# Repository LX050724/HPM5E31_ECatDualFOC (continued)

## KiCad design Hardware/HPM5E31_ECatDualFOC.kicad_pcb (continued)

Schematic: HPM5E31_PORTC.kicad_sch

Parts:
U3: HPM5E31IGN1; BGA-196_14x14_12.0x12.0mm_P0.8mm

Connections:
/ENCODER_CONN_A/ENC.CLK: U3.B7 (PC04/UART1.CTS/SPI0.SCLK/MCAN1.RXD/ESC0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); also elsewhere on the board
/ENCODER_CONN_A/ENC.CS: U3.A8 (PC05/GPTMR1.COMP2/UART1.DE/UART1.RTS/SP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); also elsewhere on the board
/ENCODER_CONN_A/ENC.MISO: U3.B8 (PC06/GPTMR0.CAPT0/UART1.RXD/I2C3.SDA/SP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); also elsewhere on the board
/ENCODER_CONN_A/ENC.MOSI: U3.A9 (PC07/GPTMR0.COMP0/UART1.TXD/I2C3.SCL/SP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); also elsewhere on the board
/ENCODER_CONN_B/ENC.CLK: U3.A11 (PC20/UART5.CTS/SPI3.SCLK/ESC0.GPI43/ESC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); also elsewhere on the board
/ENCODER_CONN_B/ENC.CS: U3.B11 (PC21/GPTMR3.COMP2/UART5.DE/UART5.RTS/SP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); also elsewhere on the board
/ENCODER_CONN_B/ENC.MISO: U3.A12 (PC22/GPTMR2.CAPT0/UART5.RXD/SPI3.MISO/E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); also elsewhere on the board
/ENCODER_CONN_B/ENC.MOSI: U3.A13 (PC23/GPTMR2.COMP0/UART5.TXD/SPI3.MOSI/E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); also elsewhere on the board
/HPM5E31_TOP/CAN0.RXD: U3.A6 (PC01/GPTMR1.CAPT0/UART0.RXD/MCAN0.RXD/E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); also elsewhere on the board
/HPM5E31_TOP/CAN0.TXD: U3.B5 (PC00/GPTMR1.COMP0/UART0.TXD/MCAN0.TXD/E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); also elsewhere on the board
/HPM5E31_TOP/FLASH.CS0: U3.D13 (PC27/UART6.CTS/SPI2.CS0/ESC0.GPI36/ESC0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); also elsewhere on the board
/HPM5E31_TOP/FLASH.D0: U3.E13 (PC29/GPTMR3.COMP3/UART7.DE/UART7.RTS/SP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); also elsewhere on the board
/HPM5E31_TOP/FLASH.D1: U3.E14 (PC28/UART7.CTS/SPI2.MISO/ESC0.GPI35/ESC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); also elsewhere on the board
/HPM5E31_TOP/FLASH.D2: U3.F14 (PC30/UART7.RXD/SPI2.DAT2/ESC0.GPI33/ESC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); also elsewhere on the board
/HPM5E31_TOP/FLASH.D3: U3.F13 (PC31/GPTMR2.COMP3/UART7.TXD/SPI2.DAT3/E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); also elsewhere on the board
/HPM5E31_TOP/FLASH.SCLK: U3.D14 (PC26/GPTMR2.COMP2/UART6.DE/UART6.RTS/SP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); also elsewhere on the board
/HPM5E31_TOP/RS485_3.DE: U3.C7 (PC13/GPTMR1.COMP3/UART3.DE/UART3.RTS/I2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); also elsewhere on the board
/HPM5E31_TOP/RS485_3.DI: U3.C8 (PC15/GPTMR0.COMP3/UART3.TXD/SPI1.DAT3/M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); also elsewhere on the board
/HPM5E31_TOP/RS485_3.RO: U3.D7 (PC14/UART3.RXD/SPI1.DAT2/MCAN3.RXD/ESC0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); also elsewhere on the board
PC2: U3.B6 (PC02/GPTMR1.COMP1/UART0.DE/UART0.RTS/I2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); also elsewhere on the board
PC3: U3.A7 (PC03/GPTMR1.CAPT1/UART0.CTS/I2C2.SDA/SP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); also elsewhere on the board
PC8: U3.B9 (PC08/GPTMR0.COMP1/UART2.TXD/I2C0.SCL/SP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); also elsewhere on the board
PC9: U3.C5 (PC09/GPTMR0.CAPT1/UART2.RXD/I2C0.SDA/SP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); also elsewhere on the board
PC10: U3.D5 (PC10/GPTMR0.COMP2/UART2.DE/UART2.RTS/SP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); also elsewhere on the board
PC11: U3.C6 (PC11/UART2.CTS/SPI1.CS0/ESC0.GPI52/ESC0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); also elsewhere on the board
PC12: U3.D6 (PC12/UART3.CTS/I2C1.SDA/SPI1.MISO/ESC0.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); also elsewhere on the board
PC16: U3.D8 (PC16/GPTMR3.COMP0/UART4.TXD/ESC0.GPI47/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)
PC17: U3.C9 (PC17/GPTMR3.CAPT0/UART4.RXD/ESC0.GPI46/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); also elsewhere on the board
PC18: U3.A10 (PC18/GPTMR3.COMP1/UART4.DE/UART4.RTS/ES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); also elsewhere on the board
PC19: U3.B10 (PC19/GPTMR3.CAPT1/UART4.CTS/SPI2.CS3/ES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)
PC24: U3.B14 (PC24/GPTMR2.COMP1/UART6.TXD/SPI2.CS2/ES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)
PC25: U3.C14 (PC25/GPTMR2.CAPT1/UART6.RXD/SPI2.CS1/ES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)

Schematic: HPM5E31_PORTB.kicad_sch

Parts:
U3: HPM5E31IGN1; BGA-196_14x14_12.0x12.0mm_P0.8mm

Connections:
/ETHERNET_PHY_P0/MII.LINK: U3.B1 (PB25/ESC0.CTR5/XPI0.CA_DQS/SDM0.DAT3/ET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); also elsewhere on the board
/ETHERNET_PHY_P0/MII.RXC: U3.C2 (PB05/MCAN1.TXD/ESC0.P0_RXCK/PWM0.P5/TRG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); also elsewhere on the board
/ETHERNET_PHY_P0/MII.RXD0: U3.E2 (PB01/MCAN0.RXD/ESC0.P0_RXD0/PWM0.P1/TRG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); also elsewhere on the board
/ETHERNET_PHY_P0/MII.RXD1: U3.D1 (PB02/I2C2.SCL/MCAN0.STBY/ESC0.P0_RXD1/P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); also elsewhere on the board
/ETHERNET_PHY_P0/MII.RXD2: U3.D2 (PB03/I2C2.SDA/MCAN1.STBY/ESC0.P0_RXD2/P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); also elsewhere on the board
/ETHERNET_PHY_P0/MII.RXD3: U3.C1 (PB04/MCAN1.RXD/ESC0.P0_RXD3/PWM0.P4/TRG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); also elsewhere on the board
/ETHERNET_PHY_P0/MII.RX_DV: U3.E1 (PB00/MCAN0.TXD/ESC0.P0_RXDV/PWM0.P0/TRG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); also elsewhere on the board
/ETHERNET_PHY_P0/MII.TXC: U3.E3 (PB06/I2C3.SDA/ESC0.P0_TXCK/PWM0.P6/TRGM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); also elsewhere on the board
/ETHERNET_PHY_P0/MII.TXD0: U3.E4 (PB07/I2C3.SCL/ESC0.P0_TXD0/PWM0.P7/TRGM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); also elsewhere on the board
/ETHERNET_PHY_P0/MII.TXD1: U3.D3 (PB08/I2C0.SCL/MCAN2.TXD/ESC0.P0_TXD1/PW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); also elsewhere on the board
/ETHERNET_PHY_P0/MII.TXD2: U3.D4 (PB09/I2C0.SDA/MCAN2.RXD/ESC0.P0_TXD2/PW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); also elsewhere on the board
/ETHERNET_PHY_P0/MII.TXD3: U3.C3 (PB10/MCAN2.STBY/ESC0.P0_TXD3/PWM1.P2/TR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); also elsewhere on the board
/ETHERNET_PHY_P0/MII.TXEN: U3.C4 (PB11/ESC0.P0_TXEN/PWM1.P3/TRGM.P11/ETH0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); also elsewhere on the board
/ETHERNET_PHY_P2/MII.RST: U3.A2 (PB24/ESC0.CTR4/XPI0.CA_CS1/SDM0.CLK3/ET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); also elsewhere on the board
PB26: U3.A3 (PB26/ESC0.CTR6/XPI0.CA_D2/QEI1.H1/SDM0.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); also elsewhere on the board
PB27: U3.B2 (PB27/ESC0.CTR7/XPI0.CA_D0/QEI1.F/SDM0.D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); also elsewhere on the board
PB28: U3.A4 (PB28/ESC0.CTR8/XPI0.CA_D1/QEI1.H0/SDM0.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); also elsewhere on the board
PB29: U3.B3 (PB29/XPI0.CA_SCLK/QEI1.Z/SDM0.DAT1/ETH0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); also elsewhere on the board
PB30: U3.A5 (PB30/ESC0.CTR7/XPI0.CA_CS0/QEI1.A/SDM0.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); also elsewhere on the board
PB31: U3.B4 (PB31/ESC0.CTR8/XPI0.CA_D3/QEI1.B/SDM0.D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); also elsewhere on the board

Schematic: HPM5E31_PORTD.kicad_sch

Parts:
U3: HPM5E31IGN1; BGA-196_14x14_12.0x12.0mm_P0.8mm

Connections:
/ENCODER_CONN_A/ENC.A: U3.B13 (PD07/I2C3.SCL/ESC0.GPI24/ESC0.GPO39/PPI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); also elsewhere on the board
/ENCODER_CONN_A/ENC.B: U3.C12 (PD06/I2C3.SDA/ESC0.GPI25/ESC0.GPO38/PPI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); also elsewhere on the board
/ENCODER_CONN_A/ENC.Z: U3.B12 (PD05/MCAN1.TXD/ESC0.GPI26/ESC0.GPO37/PP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); also elsewhere on the board
/ENCODER_CONN_B/ENC.A: U3.K12 (PD30/ESC0.GPI01/ESC0.GPO62/PPI0.DQ01/ES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); also elsewhere on the board
/ENCODER_CONN_B/ENC.B: U3.K11 (PD31/ESC0.GPI00/ESC0.GPO63/PPI0.DQ00/ES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); also elsewhere on the board
/ENCODER_CONN_B/ENC.PWR: U3.F11 (PD13/I2C1.SCL/MCAN3.STBY/ESC0.GPI18/ESC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); also elsewhere on the board
/ENCODER_CONN_B/ENC.U: U3.F12 (PD12/I2C1.SDA/ESC0.GPI19/ESC0.GPO44/PPI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); also elsewhere on the board
/ENCODER_CONN_B/ENC.V: U3.E12 (PD10/MCAN2.STBY/ESC0.GPI21/ESC0.GPO42/P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); also elsewhere on the board
/ENCODER_CONN_B/ENC.W: U3.E11 (PD11/ESC0.GPI20/ESC0.GPO43/PPI0.CS2/PWM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); also elsewhere on the board
/ENCODER_CONN_B/ENC.Z: U3.J10 (PD29/ESC0.GPI02/ESC0.GPO61/PPI0.DQ02/ES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); also elsewhere on the board
/ETHERNET_PHY_P2/MII.RXC: U3.J13 (PD21/ESC0.GPI10/ESC0.GPO53/PPI0.DQ13/ES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); also elsewhere on the board
/ETHERNET_PHY_P2/MII.RXD0: U3.H14 (PD17/ESC0.GPI14/ESC0.GPO49/PPI0.DQ09/ES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); also elsewhere on the board
/ETHERNET_PHY_P2/MII.RXD1: U3.H13 (PD18/ESC0.GPI13/ESC0.GPO50/PPI0.DQ12/ES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); also elsewhere on the board
/ETHERNET_PHY_P2/MII.RXD2: U3.H12 (PD19/ESC0.GPI12/ESC0.GPO51/PPI0.DQ11/ES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); also elsewhere on the board
/ETHERNET_PHY_P2/MII.RXD3: U3.J14 (PD20/ESC0.GPI11/ESC0.GPO52/PPI0.DQ14/ES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); also elsewhere on the board
/ETHERNET_PHY_P2/MII.RX_DV: U3.G12 (PD16/ESC0.GPI15/ESC0.GPO48/PPI0.DQ10/ES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); also elsewhere on the board
/ETHERNET_PHY_P2/MII.RX_ER: U3.J12 (PD22/ESC0.GPI09/ESC0.GPO54/PPI0.DQ15/ES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); also elsewhere on the board
/ETHERNET_PHY_P2/MII.TXC: U3.F10 (PD23/ESC0.GPI08/ESC0.GPO55/PPI0.DM0/ESC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); also elsewhere on the board
/ETHERNET_PHY_P2/MII.TXD0: U3.G11 (PD24/ESC0.GPI07/ESC0.GPO56/PPI0.DQ06/ES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); also elsewhere on the board
/ETHERNET_PHY_P2/MII.TXD1: U3.G10 (PD25/ESC0.GPI06/ESC0.GPO57/PPI0.DQ07/ES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); also elsewhere on the board
/ETHERNET_PHY_P2/MII.TXD2: U3.H11 (PD26/ESC0.GPI05/ESC0.GPO58/PPI0.DQ05/ES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); also elsewhere on the board
/ETHERNET_PHY_P2/MII.TXD3: U3.H10 (PD27/ESC0.GPI04/ESC0.GPO59/PPI0.DQ04/ES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); also elsewhere on the board
/ETHERNET_PHY_P2/MII.TXEN: U3.J11 (PD28/ESC0.GPI03/ESC0.GPO60/PPI0.DQ03/ES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); also elsewhere on the board
/HPM5E31_TOP/CAN3.RXD: U3.G14 (PD14/MCAN3.RXD/ESC0.GPI17/ESC0.GPO46/PP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); also elsewhere on the board
/HPM5E31_TOP/CAN3.TXD: U3.G13 (PD15/MCAN3.TXD/ESC0.GPI16/ESC0.GPO47/PP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); also elsewhere on the board
PD0: U3.D9 (PD00/MCAN0.TXD/ESC0.GPI31/ESC0.GPO32/PP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)
PD1: U3.C10 (PD01/MCAN0.RXD/ESC0.GPI30/ESC0.GPO33/PP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); also elsewhere on the board
PD2: U3.D10 (PD02/I2C2.SCL/MCAN0.STBY/ESC0.GPI29/ESC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); also elsewhere on the board
PD3: U3.C11 (PD03/I2C2.SDA/MCAN1.STBY/ESC0.GPI28/ESC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); also elsewhere on the board
PD4: U3.D11 (PD04/MCAN1.RXD/ESC0.GPI27/ESC0.GPO36/PP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); also elsewhere on the board
PD8: U3.C13 (PD08/I2C0.SCL/MCAN2.TXD/ESC0.GPI23/ESC0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)
PD9: U3.D12 (PD09/I2C0.SDA/MCAN2.RXD/ESC0.GPI22/ESC0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); also elsewhere on the board

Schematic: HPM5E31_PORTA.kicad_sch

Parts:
C5, C6, C7, C8: 100nF,10V; C_0201_0603Metric
U3: HPM5E31IGN1; BGA-196_14x14_12.0x12.0mm_P0.8mm

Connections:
+3.3V: C5.1, C6.1, C7.1, C8.1, U3.E6 (VIO_B01), U3.E7 (VIO_B01), U3.E8 (VIO_B01), U3.E9 (VIO_B01), U3.K6 (VIO_B01); also elsewhere on the board
/ENCODER_CONN_A/ENC.PWR: U3.K2 (PA19/GPTMR3.CAPT1/UART4.CTS/SPI3.CS3/ES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); also elsewhere on the board
/ENCODER_CONN_A/ENC.U: U3.H1 (PA22/GPTMR2.CAPT0/UART5.RXD/SPI2.MISO/E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); also elsewhere on the board
/ENCODER_CONN_A/ENC.V: U3.J2 (PA21/GPTMR3.COMP2/UART5.DE/UART5.RTS/SP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); also elsewhere on the board
/ENCODER_CONN_A/ENC.W: U3.J1 (PA20/UART5.CTS/SPI2.SCLK/ESC0.P0_RXD3/S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); also elsewhere on the board
/ETHERNET_PHY_P0/MII.RX_ER: U3.H2 (PA23/GPTMR2.COMP0/UART5.TXD/SPI2.MOSI/E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); also elsewhere on the board
/ETHERNET_PHY_P2/MII.MDC: U3.H5 (PA31/GPTMR2.COMP3/UART7.TXD/SPI3.DAT3/E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); also elsewhere on the board
/ETHERNET_PHY_P2/MII.MDIO: U3.H4 (PA30/UART7.RXD/SPI3.DAT2/ESC0.MDIO/ETH0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); also elsewhere on the board
/HPM5E31_TOP/RS485_4.DE: U3.K1 (PA18/GPTMR3.COMP1/UART4.DE/UART4.RTS/ES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); also elsewhere on the board
/HPM5E31_TOP/RS485_4.DI: U3.L1 (PA16/GPTMR3.COMP0/UART4.TXD/ESC0.P0_RXD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); also elsewhere on the board
/HPM5E31_TOP/RS485_4.RO: U3.L2 (PA17/GPTMR3.CAPT0/UART4.RXD/ESC0.P0_RXD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); also elsewhere on the board
/HPM5E31_TOP/RS485_6.DE: U3.J3 (PA26/GPTMR2.COMP2/UART6.DE/UART6.RTS/SP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); also elsewhere on the board
/HPM5E31_TOP/RS485_6.DI: U3.K3 (PA24/GPTMR2.COMP1/UART6.TXD/SPI3.CS2/ES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); also elsewhere on the board
/HPM5E31_TOP/RS485_6.RO: U3.K4 (PA25/GPTMR2.CAPT1/UART6.RXD/SPI3.CS1/ES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); also elsewhere on the board
GND: C5.2, C6.2, C7.2, C8.2; also elsewhere on the board
PA0: U3.G2 (PA00/GPTMR1.COMP0/UART0.TXD/MCAN0.TXD/P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); also elsewhere on the board
PA1: U3.G3 (PA01/GPTMR1.CAPT0/UART0.RXD/MCAN0.RXD/P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); also elsewhere on the board
PA2: U3.G4 (PA02/GPTMR1.COMP1/UART0.DE/UART0.RTS/I2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); also elsewhere on the board
PA3: U3.G5 (PA03/GPTMR1.CAPT1/UART0.CTS/I2C2.SDA/MC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); also elsewhere on the board
PA4: U3.F2 (PA04/UART1.CTS/SPI1.SCLK/MCAN1.RXD/PWM0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); also elsewhere on the board
PA5: U3.F3 (PA05/GPTMR1.COMP2/UART1.DE/UART1.RTS/SP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); also elsewhere on the board
PA6: U3.F4 (PA06/GPTMR0.CAPT0/UART1.RXD/I2C3.SDA/SP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); also elsewhere on the board
PA7: U3.F5 (PA07/GPTMR0.COMP0/UART1.TXD/I2C3.SCL/SP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); also elsewhere on the board
PA8: U3.G1 (PA08/GPTMR0.COMP1/UART2.TXD/I2C0.SCL/MC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); also elsewhere on the board
PA9: U3.F1 (PA09/GPTMR0.CAPT1/UART2.RXD/I2C0.SDA/MC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); also elsewhere on the board
PA27: U3.J4 (PA27/UART6.CTS/SPI3.CS0/ESC0.P0_TXD2/QE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)
PA28: U3.J5 (PA28/UART7.CTS/SPI3.MISO/ESC0.P0_TXD3/E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)
PA29: U3.H3 (PA29/GPTMR3.COMP3/UART7.DE/UART7.RTS/SP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)

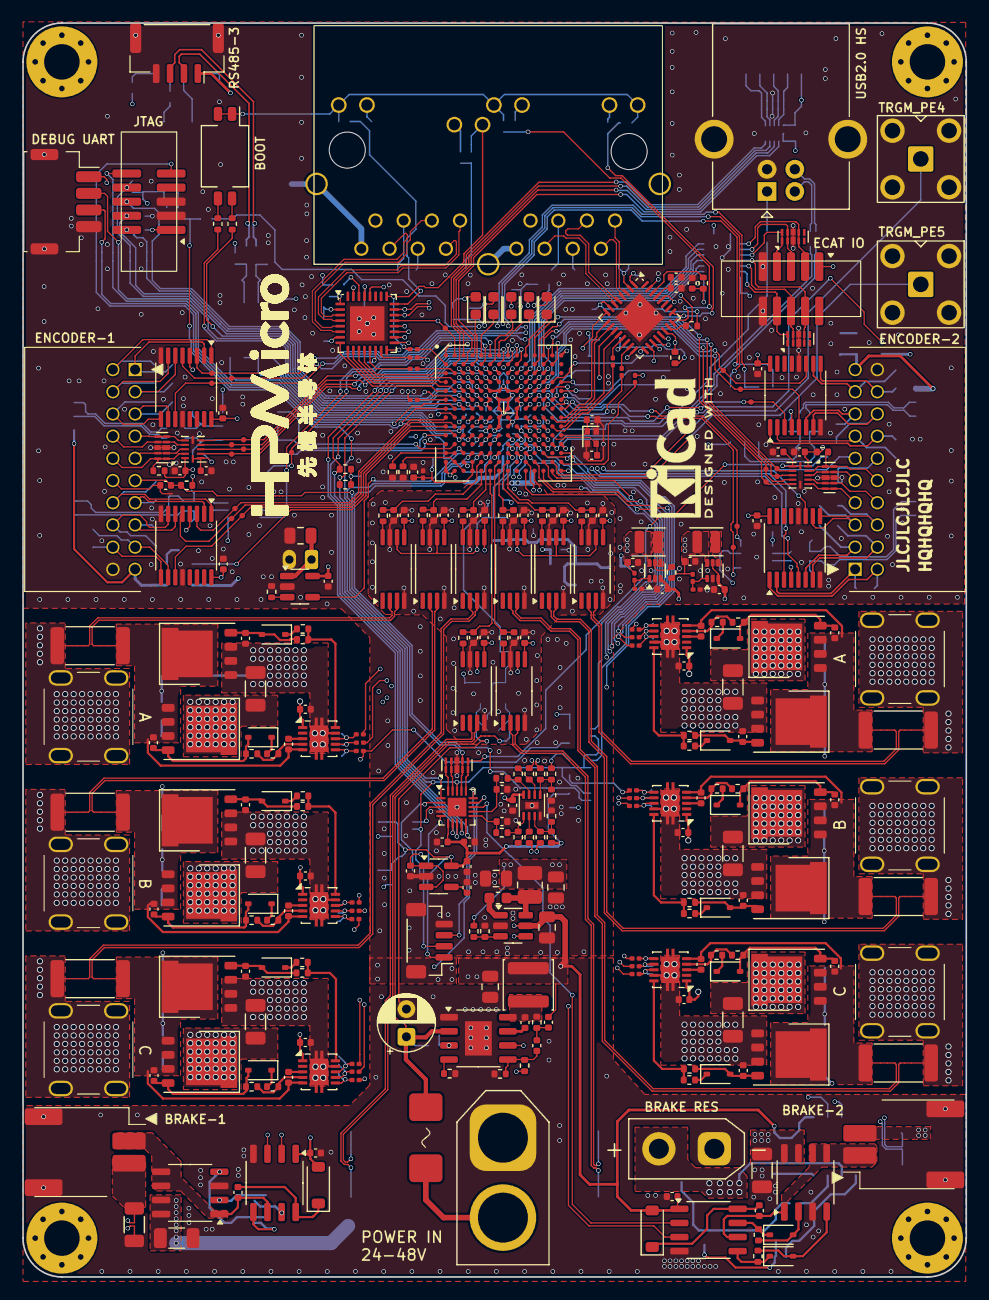
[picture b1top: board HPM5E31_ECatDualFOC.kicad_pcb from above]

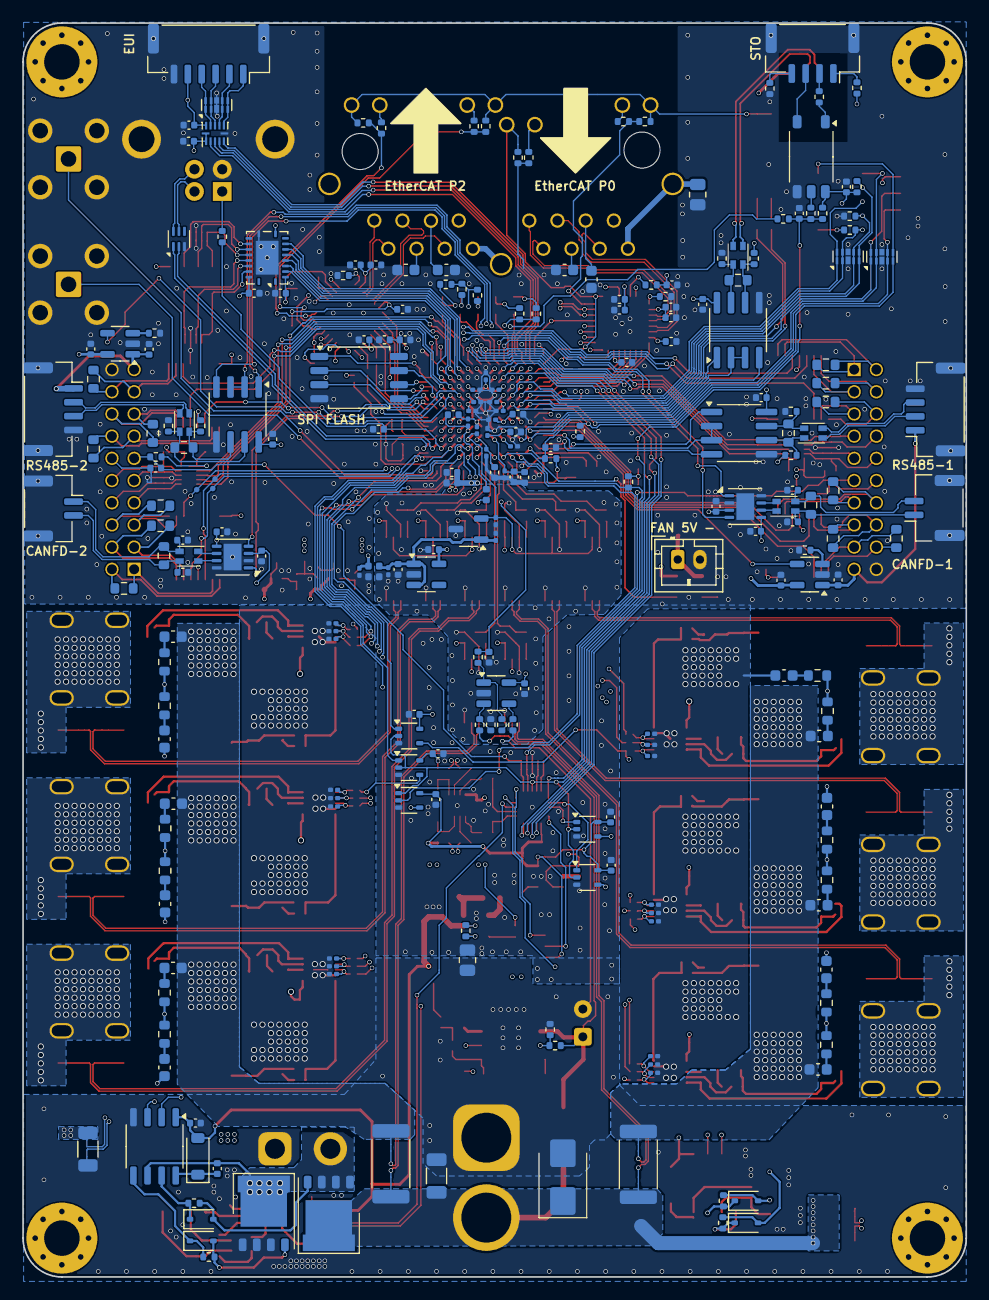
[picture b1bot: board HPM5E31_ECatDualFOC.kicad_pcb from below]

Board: 4 copper layers, 85.0 x 113.0 mm, 585 parts (250 on the bottom side), 455 nets.

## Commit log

2025-06-24 init
2025-06-25 新增ESC IO引出，ESC CTR LED，EUI接口
    编码器接口电源输出加保险，SPI加ESD
    PY32ADC外部接口加ESD
2025-06-27 调整引脚，拉线
2025-07-07 修存档拉线
2025-07-13 拉线，增加刹车电阻
2025-08-04 拉线，删除电荷泵，修改10Vdcdc斜坡补偿
2025-08-17 添加母线电压测量
2025-08-17 修饰，第一次打板
2025-09-03 修改PCB，上传py32抱闸驱动代码，上传HPM board
    调整抱闸驱动栅极电阻
    急停光耦增加上拉电阻和滤波电路
2025-09-19 PCB和foc_demo
    PCB：
    部分信号增加测试点
    半桥增加栅极电容和RC吸收（待定），泄放mos是否需要栅极电容待测
    软件：
    增加foc_demo半成品
2025-09-21 foc_demo: pwm和adc功能补全，强拖和基本电流采样功能跑通
2025-10-01 初步实现电流环
    新增vofa协议实现
    pwm补全强制输出控制
    支持电流校准，电流采样序列切换
2025-10-03 PCB优化，修改母线电流采样电阻为2mR，栅极驱动器输入pwm增加滤波防干扰，其他少量优化
2025-10-05 PCB修改栅极电阻，增加上侧RC吸收电路，同步修改软件死区时间到150ns
2025-10-05 PCB：网口替换为HR911205C
2025-10-08 更改网口接地，更改RC吸收封装
2025-10-09 相线铜箔增加开窗
2025-10-12 Update README with product specs and images
    Added product specifications, power tree, and hardware architecture sections to README.md. Included three new images in README.assets and updated instructions regarding JLink version requirements.
2025-10-12 Update hardware architecture diagram in README
2025-10-12 PCB：风扇增加控制IO，泄放驱动增加使能引脚，485编码器电源接入控制
2025-10-12 readme框图补全风扇开关
